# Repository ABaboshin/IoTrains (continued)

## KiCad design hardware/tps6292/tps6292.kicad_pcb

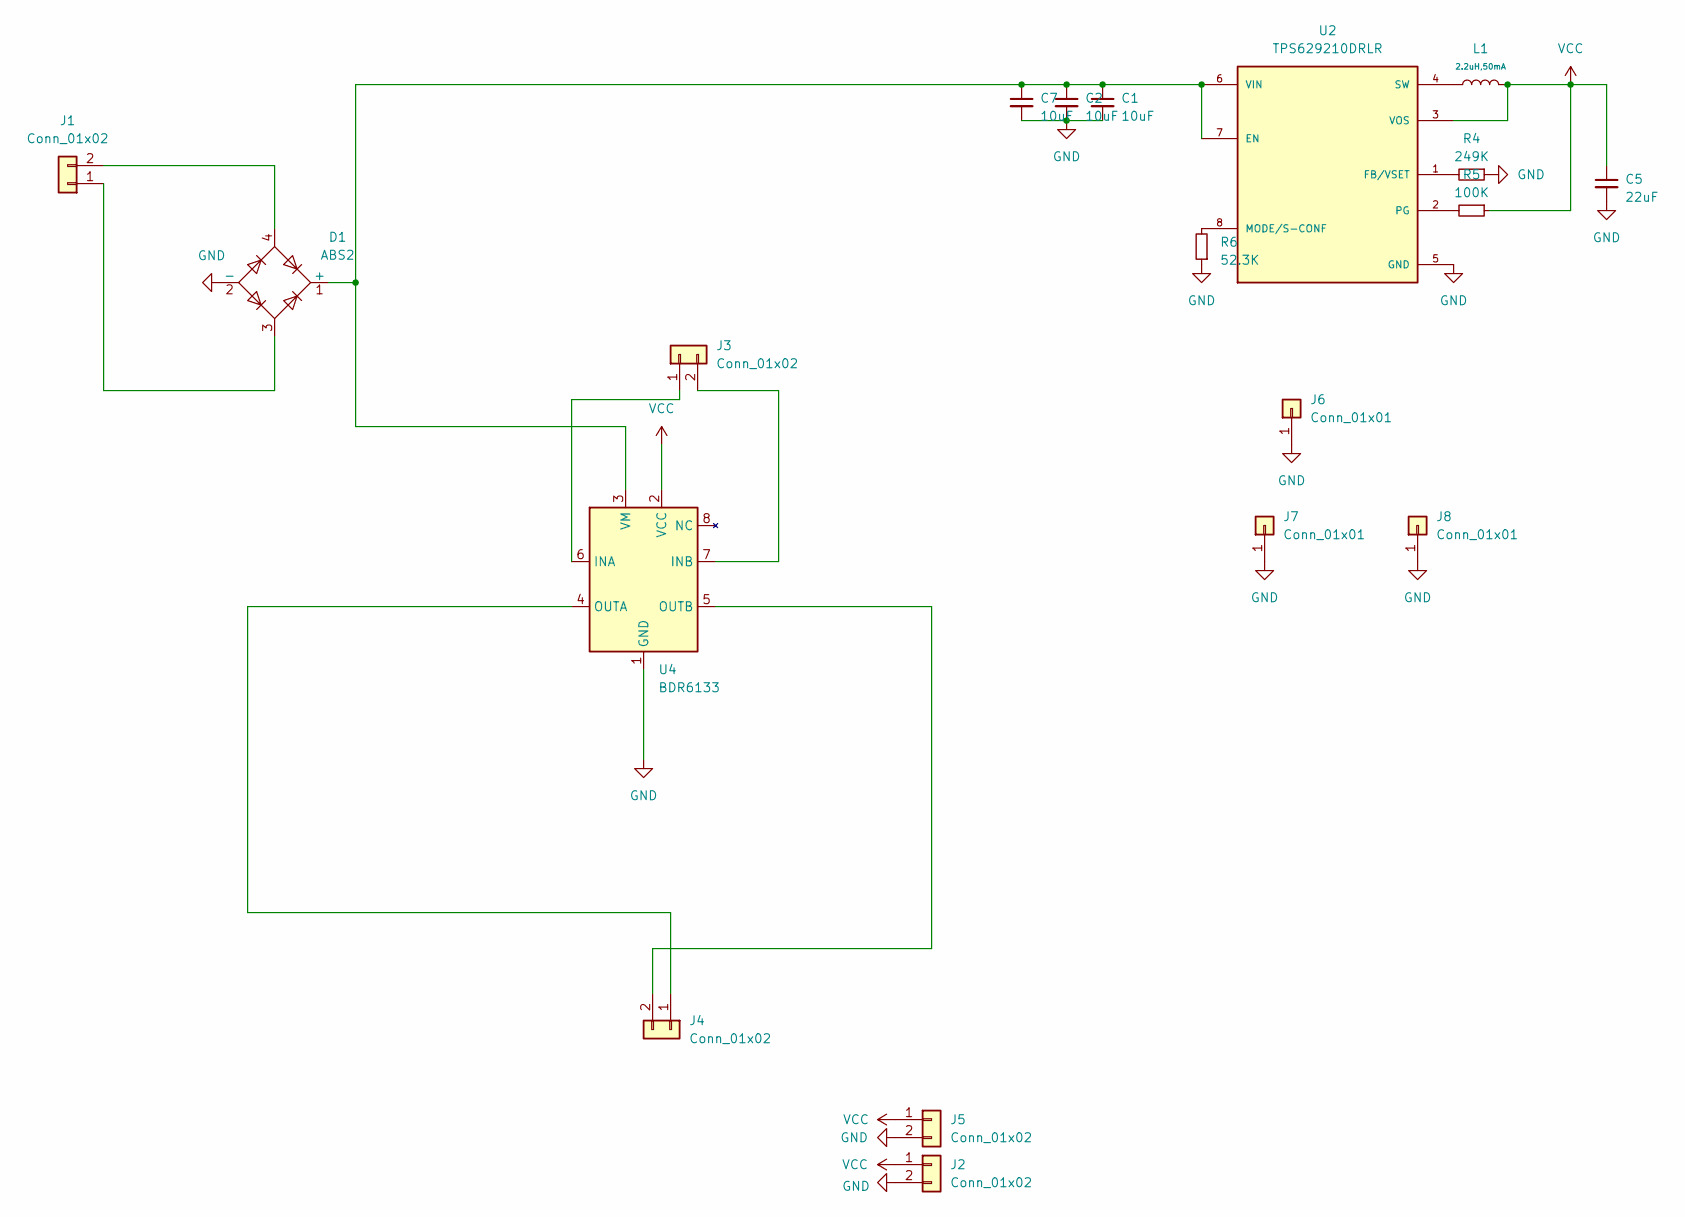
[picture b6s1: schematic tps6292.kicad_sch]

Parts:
C1, C2, C7: 10uF; C_0603_1608Metric; LCSC C96446
C5: 22uF; C_0603_1608Metric; LCSC C59461
D1: ABS2; Diode_Bridge_Diotec_ABS
J1, J2, J4, J5: Conn_01x02; S2BZRLFSN; LCSC C157930
J3: Conn_01x02; JST_SHL_SM02B-SHLS-TF_1x02-1MP_P1.00mm_Horizontal; LCSC C160402
J6, J7, J8: Conn_01x01; PinHeader_1x01_P1.00mm_Vertical
L1: 2.2uH,50mA; L_0805; Tolerance ±10%; Part CMI201209U2R2KT; LCSC C1043
R4: 249K; R_0603_1608Metric; LCSC C22918
R5: 100K; R_0603_1608Metric; LCSC C25803
R6: 52.3K; R_0603_1608Metric; LCSC C23198
U2: TPS629210DRLR; SOT50P160X60-8N; PARTREV B; LCSC C5219301
U4: BDR6133; SOIC-8-1EP_3.9x4.9mm_P1.27mm_EP2.41x3.3mm_ThermalVias; LCSC Part # C2687793

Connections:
GND: C1.2, C2.2, C5.2, C7.2, D1.2 (-), J2.2, J5.2, J6.1, J7.1, J8.1, R4.1, R6.1, U2.5 (GND), U4.1 (GND), U4.9 (GND)
unnamed: C1.1, C2.1, C7.1, D1.1 (+), U2.6 (VIN), U2.7 (EN), U4.3 (VM)
unnamed: D1.3, J1.1
unnamed: D1.4, J1.2
unnamed: J3.1, U4.6 (INA)
unnamed: J3.2, U4.7 (INB)
unnamed: J4.1, U4.4 (OUTA)
unnamed: J4.2, U4.5 (OUTB)
unnamed: R4.2, U2.1 (FB/VSET)
unnamed: R6.2, U2.8 (MODE/S-CONF)
unnamed: R5.2, U2.2 (PG)
unnamed: L1.1, U2.4 (SW)
VCC: C5.1, J2.1, J5.1, L1.2, R5.1, U2.3 (VOS), U4.2 (VCC)

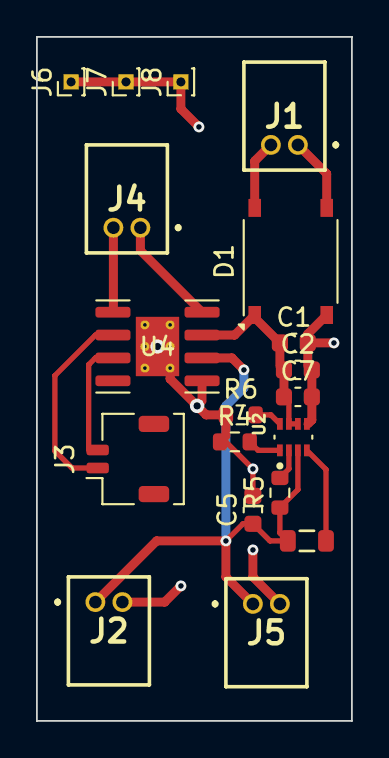
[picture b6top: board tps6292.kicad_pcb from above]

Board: 2 copper layers, 17.5 x 38.0 mm, 19 parts (0 on the bottom side), 13 nets.

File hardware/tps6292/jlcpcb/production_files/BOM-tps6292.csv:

Comment,Designator,Footprint,LCSC,Quantity
100K,R5,R_0603_1608Metric,C25803,1
10uF,"C1,C2,C7",C_0603_1608Metric,C96446,3
"2.2uH,50mA",L1,L_0805,C1043,1
22uF,C5,C_0603_1608Metric,C59461,1
249K,R4,R_0603_1608Metric,C22918,1
52.3K,R6,R_0603_1608Metric,C23198,1
ABS2,D1,Diode_Bridge_Diotec_ABS,C84159,1
BDR6133,U4,SOIC-8-1EP_3.9x4.9mm_P1.27mm_EP2.41x3.3mm_ThermalVias,C2687793,1
Conn_01x02,"J1,J2,J4,J5",JST_ZH_S2B-ZR-SM4A-TF_1x02-1MP_P1.50mm_Horizontal,C157930,4
Conn_01x02,J3,JST_SHL_SM02B-SHLS-TF_1x02-1MP_P1.00mm_Horizontal,C160402,1
TPS629210DRLR,U2,SOT50P160X60-8N,C5219301,1
Conn_01x01,J8,PinHeader_1x01_P1.00mm_Vertical,,1
Conn_01x01,J7,PinHeader_1x01_P1.00mm_Vertical,,1
Conn_01x01,J6,PinHeader_1x01_P1.00mm_Vertical,,1

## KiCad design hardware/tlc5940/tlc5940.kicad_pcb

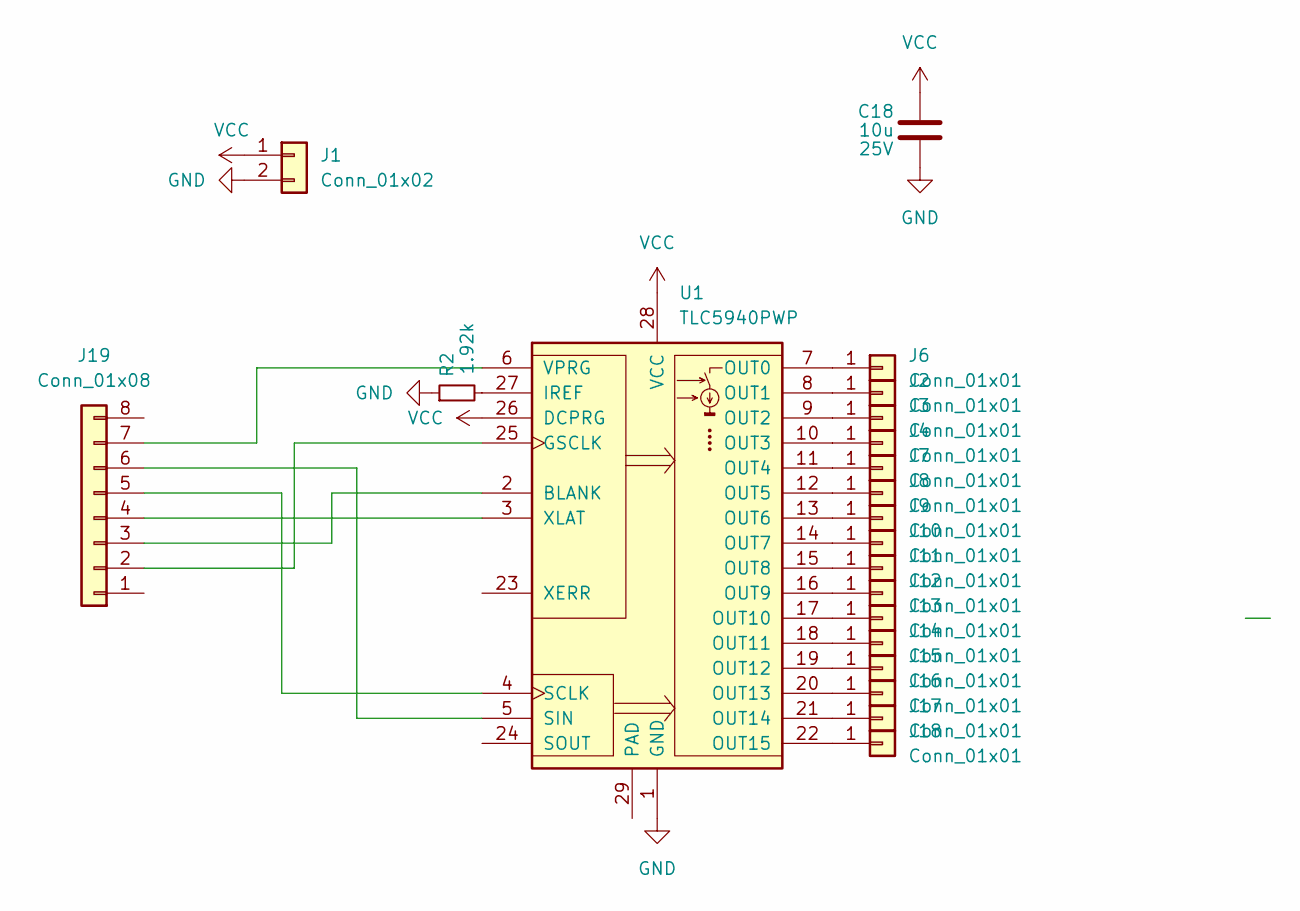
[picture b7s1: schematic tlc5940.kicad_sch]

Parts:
C18: 10u; C_0603_1608Metric; Voltage 25V; LCSC Part # C96446
J1: Conn_01x02; S2BZRLFSN; LCSC C157930
J2, J3, J4, J6, J7, J8, J9, J10, J11, J12, J13, J14, J15, J16, J17, J18: Conn_01x01; PinHeader_1x01_P1.00mm_Vertical
J19: Conn_01x08; JST_SHL_SM08B-SHLS-TF_1x08-1MP_P1.00mm_Horizontal
R2: 1.92k; R_0402_1005Metric
U1: TLC5940PWP; HTSSOP-28-1EP_4.4x9.7mm_P0.65mm_EP3.4x9.5mm_Mask2.4x6.17mm_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

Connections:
GND: C18.2, J1.2, R2.1, U1.1 (GND)
unnamed: J2.1, U1.8 (OUT1)
unnamed: J3.1, U1.9 (OUT2)
unnamed: J4.1, U1.10 (OUT3)
unnamed: J6.1, U1.7 (OUT0)
unnamed: J7.1, U1.11 (OUT4)
unnamed: J8.1, U1.12 (OUT5)
unnamed: J9.1, U1.13 (OUT6)
unnamed: J10.1, U1.14 (OUT7)
unnamed: J11.1, U1.15 (OUT8)
unnamed: J12.1, U1.16 (OUT9)
unnamed: J13.1, U1.17 (OUT10)
unnamed: J14.1, U1.18 (OUT11)
unnamed: J15.1, U1.19 (OUT12)
unnamed: J16.1, U1.20 (OUT13)
unnamed: J17.1, U1.21 (OUT14)
unnamed: J18.1, U1.22 (OUT15)
unnamed: J19.2, U1.25 (GSCLK)
unnamed: J19.3, U1.2 (BLANK)
unnamed: J19.4, U1.3 (XLAT)
unnamed: J19.5, U1.4 (SCLK)
unnamed: J19.6, U1.5 (SIN)
unnamed: J19.7, U1.6 (VPRG)
unnamed: R2.2, U1.27 (IREF)
VCC: C18.1, J1.1, U1.26 (DCPRG), U1.28 (VCC)

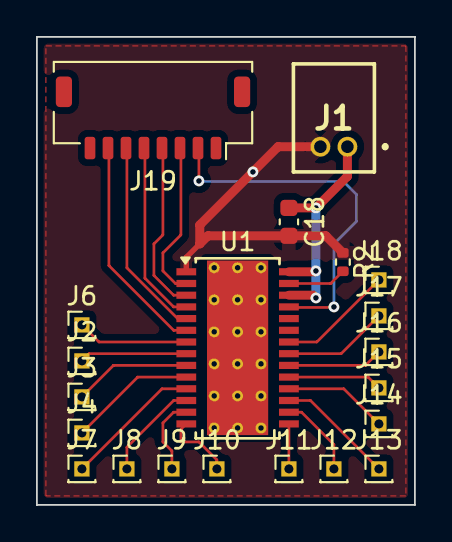
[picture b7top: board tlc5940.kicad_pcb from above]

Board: 2 copper layers, 21.0 x 26.0 mm, 21 parts (0 on the bottom side), 25 nets.

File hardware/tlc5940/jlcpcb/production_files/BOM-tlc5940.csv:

Comment,Designator,Footprint,LCSC,Quantity
1.92k,R2,R_0402_1005Metric,C4109,1
10u,C18,C_0603_1608Metric,C96446,1
Conn_01x02,J1,S2BZRLFSN,C157930,1
Conn_01x08,J19,JST_SHL_SM08B-SHLS-TF_1x08-1MP_P1.00mm_Horizontal,C160407,1
TLC5940PWP,U1,HTSSOP-28-1EP_4.4x9.7mm_P0.65mm_EP3.4x9.5mm_Mask2.4x6.17mm_ThermalVias,C181653,1
Conn_01x01,J3,PinHeader_1x01_P1.00mm_Vertical,,1
Conn_01x01,J2,PinHeader_1x01_P1.00mm_Vertical,,1
Conn_01x01,J18,PinHeader_1x01_P1.00mm_Vertical,,1
Conn_01x01,J17,PinHeader_1x01_P1.00mm_Vertical,,1
Conn_01x01,J16,PinHeader_1x01_P1.00mm_Vertical,,1
Conn_01x01,J15,PinHeader_1x01_P1.00mm_Vertical,,1
Conn_01x01,J14,PinHeader_1x01_P1.00mm_Vertical,,1
Conn_01x01,J13,PinHeader_1x01_P1.00mm_Vertical,,1
Conn_01x01,J12,PinHeader_1x01_P1.00mm_Vertical,,1
Conn_01x01,J11,PinHeader_1x01_P1.00mm_Vertical,,1
Conn_01x01,J10,PinHeader_1x01_P1.00mm_Vertical,,1
Conn_01x01,J9,PinHeader_1x01_P1.00mm_Vertical,,1
Conn_01x01,J8,PinHeader_1x01_P1.00mm_Vertical,,1
Conn_01x01,J7,PinHeader_1x01_P1.00mm_Vertical,,1
Conn_01x01,J4,PinHeader_1x01_P1.00mm_Vertical,,1
Conn_01x01,J6,PinHeader_1x01_P1.00mm_Vertical,,1

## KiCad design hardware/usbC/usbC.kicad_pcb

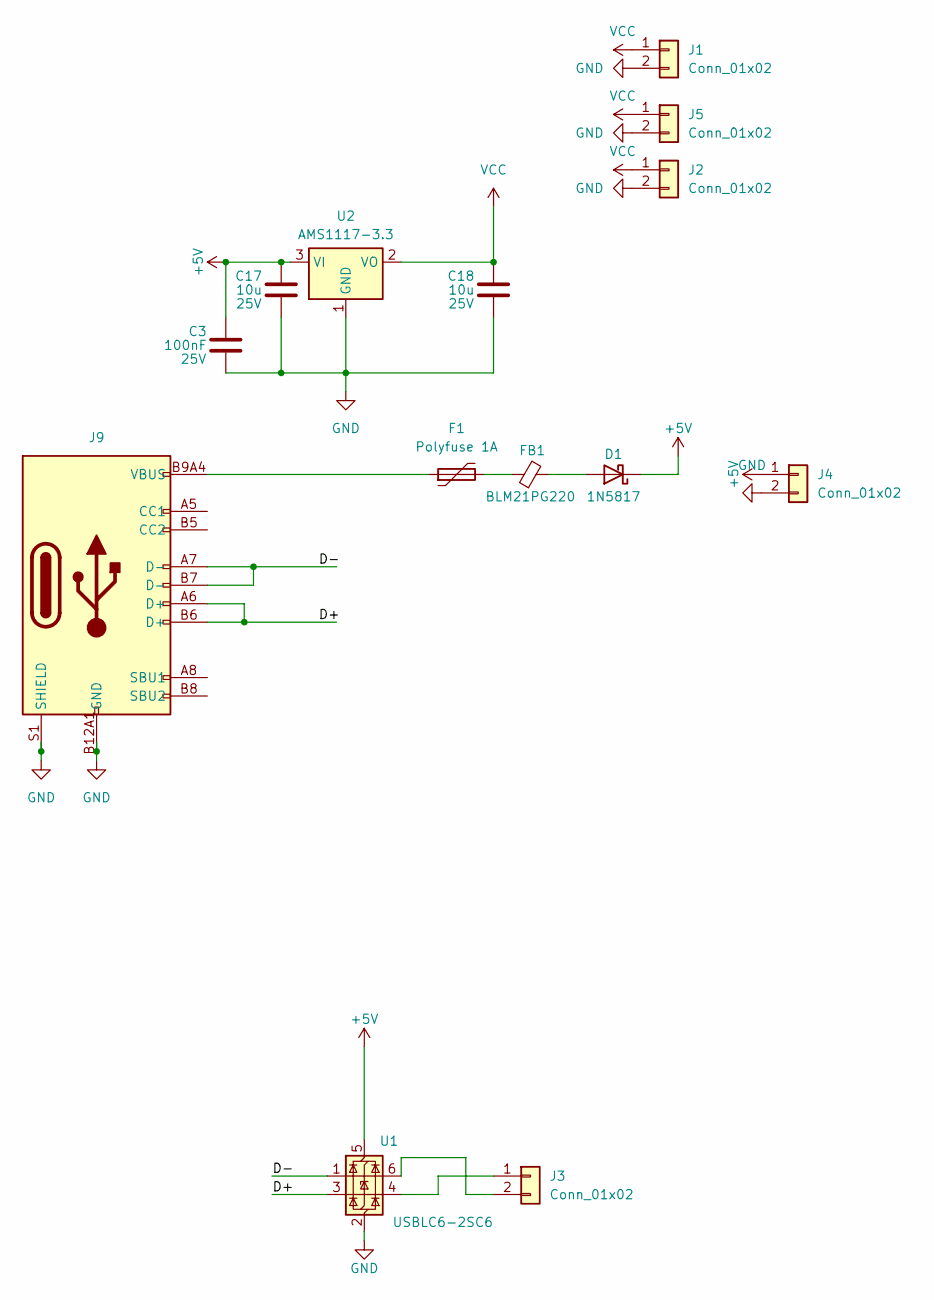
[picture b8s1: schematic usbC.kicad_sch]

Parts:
C3: 100nF; C_0603_1608Metric; Voltage 25V; LCSC C96446
C17, C18: 10u; C_0603_1608Metric; Voltage 25V; LCSC C96446
D1: 1N5817; SOD2613X110N; LCSC C2828424
F1: Polyfuse 1A; Fuse_1206_3216Metric; LCSC C1020
FB1: BLM21PG220; L_0805_2012Metric; LCSC C88993
J1, J2, J4, J5: Conn_01x02; S2BZRLFSN; LCSC C157930
J3: Conn_01x02; JST_SHL_SM02B-SHLS-TF_1x02-1MP_P1.00mm_Horizontal; LCSC C160402
J9: Connector, USB-TYPE-C-16P; TYPE-C-SMD_HX-TYPE-C-16PIN; LCSC C2927039
U1: USBLC6-2SC6; SOT-23-6; LCSC C2687116
U2: AMS1117-3.3; SOT-89-3; LCSC C7473143

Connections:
+5V: C3.1, C17.1, D1.1 (K), J4.1, U1.5 (VBUS), U2.3 (VI)
/D+: J9.A6 (D+), J9.B6 (D+), U1.3 (I/O2)
/D-: J9.A7 (D-), J9.B7 (D-), U1.1 (I/O1)
GND: C3.2, C17.2, C18.2, J1.2, J2.2, J4.2, J5.2, J9.A12B1 (GND), J9.B12A1 (GND), J9.S1 (SHIELD), U1.2 (GND), U2.1 (GND)
unnamed: D1.2 (A), FB1.2
unnamed: F1.1, J9.A9B4 (VBUS), J9.B9A4 (VBUS)
unnamed: F1.2, FB1.1
unnamed: J3.1, U1.4 (I/O2)
unnamed: J3.2, U1.6 (I/O1)
VCC: C18.1, J1.1, J2.1, J5.1, U2.2 (VO)

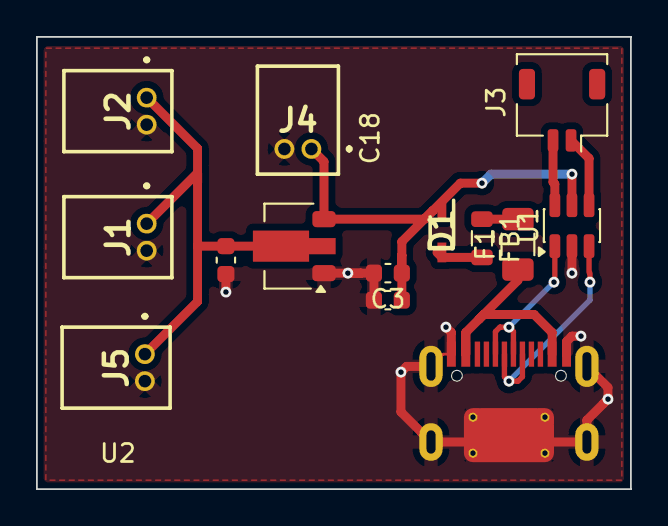
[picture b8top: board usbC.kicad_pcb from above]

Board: 2 copper layers, 33.0 x 25.1 mm, 14 parts (0 on the bottom side), 10 nets.

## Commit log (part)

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2024-01-29 esp32c3
2024-01-31 wip pio
2024-01-31 basic json schema
2024-01-31 sample cu
2024-01-31 dummy web app
2024-01-31 typescript + generate by json schema
2024-02-01 webpack
2024-02-01 share between frontend and backend
2024-02-01 frontend typescript
2024-02-01 customize schema
2024-02-01 try join
2024-02-01 Revert "try join"
    This reverts commit 8b778f53f09182690da3ec624039e0874b287c5a.
2024-02-02 send from device to backend over mqtt
2024-02-02 send report on timer
2024-02-02 device - backend - frontend
2024-02-02 state
2024-02-02 send status
2024-02-02 expose states to backend
2024-02-02 fix backend
2024-02-02 more fixes
2024-02-04 start mp3
2024-02-04 control unit loop
2024-02-04 rename
2024-02-04 improve schema generation
2024-02-04 download mp3
2024-02-04 documentation
2024-02-04 initial version (#1)
2024-02-07 feat: rfid reader + events queue
2024-02-07 feat: rfid reader + events queue (#2)
2024-02-07 feat: stop play mp3
2024-02-07 feat: stop play mp3 (#3)
2024-02-07 pass command by pointer
2024-02-07 generate from json for hierarchy
2024-02-08 generate to_json for hierarchy
2024-02-08 update typescript
2024-02-08 feat: improve hierarchy parsing (#4)
2024-02-09 fix: play mp3 on esp32
2024-02-09 fix from_json/to_json
2024-02-09 fix: play mp3 on esp32 (#5)
    * fix: play mp3 on esp32
    * fix from_json/to_json
2024-02-09 feat: turnout
2024-02-12 ﻿fix: play mp3 on esp32 (#5)
    * fix: play mp3 on esp32
    * fix from_json/to_json
2024-02-12 feat: turnout (#6)
2024-02-12 json dependency
2024-02-13 gitignore
2024-02-13 refactor: extract library (#7)
2024-02-15 feat: add esp32 wroom, improve mp3
2024-02-15 feat: add esp32 wroom, improve mp3 (#8)
2024-02-18 feat: pwm audio
2024-02-18 feat: pwm audio (#9)
2024-02-18 feat: ldo
2024-02-18 feat: ldo (#10)
2024-02-21 fix: esp32-c3 i2s
2024-02-21 fix: esp32-c3 i2s (#11)
2024-02-22 feat: basic train, documentation
2024-02-22 feat: basic train, documentation (#12)
2024-02-22 feat: introduce capabilities
2024-02-22 feat: introduce capabilities (#13)
2024-02-22 feat: fallback action if no connection
2024-02-22 feat: fallback action if no connection (#14)
2024-02-24 fix: set discriminator
2024-02-24 fix: set discriminator (#15)
2024-02-28 feat: VT95 train
2024-02-28 feat: VT95 train (#16)
2024-02-28 feat: drop down 4 layer
2024-02-28 ams1117
2024-02-28 feat: 4 layers PCB + AMS1117 (#17)
    * feat: drop down 4 layer
    * ams1117
2024-02-29 fix: apply jlcpcb rules
2024-02-29 fix: apply jlcpcb rules (#18)
2024-03-02 feat: MX1508 motor driver
2024-03-02 feat: MX1508 motor driver (#19)
2024-03-05 feat: light
2024-03-05 feat: light (#20)
2024-03-05 feat OTA
2024-03-05 feat OTA (#21)
    * feat OTA
    * gitignore
2024-03-09 feat: multiple rfid, sample train station
2024-03-09 add turnout
2024-03-10 dockerfile
2024-03-10 fix mp3 url player
2024-03-10 fix mp3 player progmem
2024-03-10 push docker
2024-03-10 fix mqtt client buffer
2024-03-11 todo
2024-03-11 feat: multiple rfid, sample train station, fix multiple mp3, docker (#22)
    * feat: multiple rfid, sample train station
    * add turnout
    * dockerfile
    * fix mp3 url player
    * fix mp3 player progmem
    * push docker
2024-03-12 feat: bogie with gears
2024-03-14 bogie with vertical motor
2024-03-14 motor holders
2024-03-14 horizontal bogie
2024-03-14 81-717-714 wall part1
2024-03-14 whole wall test1
2024-03-14 fix to print part1
2024-03-14 fix to print side wall
2024-03-17 part1 with constraints
2024-03-17 side part rebuild
2024-03-17 roof
2024-03-17 seats
2024-03-17 base
2024-03-17 control panel
2024-03-20 tail
2024-03-20 seet6
2024-03-21 hide
2024-03-21 resize roof
2024-03-21 two side parts
2024-03-22 3 sketches
2024-03-22 3 sketches v2
2024-03-22 separator
2024-03-22 seaparator big
2024-03-23 face
2024-03-23 check sizes 1
2024-03-23 714 and 717 full
2024-03-23 vertical bogie recalc
2024-03-23 horizontal bogie recalc
2024-03-25 generate stl
2024-03-25 feat: 81-717/714, bogies (#23)
2024-06-15 81-717/714
2025-05-18 wip power supply
2025-05-19 ldo + motor driver
2025-05-19 gnd zones
2025-05-30 repalce ldo and diode bridge
2025-07-27 add motor driver wip
2025-07-27 feat: rebuild ldo + motordriver (#1)
2025-07-27 feat: cleanup
2025-07-27 feat: cleanup (#2)
2025-07-27 v0.0.0
2025-07-27 pretties
2025-07-27 docker build
2025-07-27 add vite
2025-07-27 tailwind
    todo
    zusstand
    esling config
2025-07-27 cleanup
    TODO
    use zustand
2025-07-27 fix build firmware
2026-02-15 esp32
2026-02-16 TPS629210DRLR
2026-02-22 fix DRC
2026-02-23 wip: - ldo with ams - ldo with TPS629210DRLR - esp32 with usb and connectors - tlc5940
2026-02-24 ams1117 + jst sh
    TODO:
    - jst 1.5mm
    - TPS629210DRLR
    - esp32
    - led driver
2026-02-25 update connectors
2026-02-25 tps6292
2026-02-25 esp32 wip
2026-02-26 regenerate jlcpcb
2026-02-28 simplify usb
2026-02-28 simplify pins and buttons
2026-02-28 esp32 routing
2026-02-28 power supply track sizes
2026-03-01 esp32 rebuild connectors
2026-03-01 some fixes
2026-03-01 tlc5940
2026-03-01 adjustments
2026-03-01 jlcpcb wip
2026-03-04 replace connectors
2026-04-26 tlc5940 code
2026-04-26 fix usb connectors
2026-04-26 esp32 v2
2026-04-29 usbc
2026-04-29 update usb
2026-04-29 cleanup
2026-05-11 wip esp32 v1
2026-05-11 wip esp32 v2
2026-05-18 copy
2026-05-18 Revert "wip esp32 v1"
    This reverts commit 4981c68ebba1a87f50308cda0493b3bcd30c48b4.
2026-05-18 usbc production
2026-06-14 feat: esp32, tlc5940, tps6292/BDR6133, usbc (#3)
2026-06-14 update deps
2026-06-15 adjust pcb max size
